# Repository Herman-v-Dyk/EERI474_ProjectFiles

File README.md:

All the files of my final year project is in this repository.

JH van Dyk
30254906

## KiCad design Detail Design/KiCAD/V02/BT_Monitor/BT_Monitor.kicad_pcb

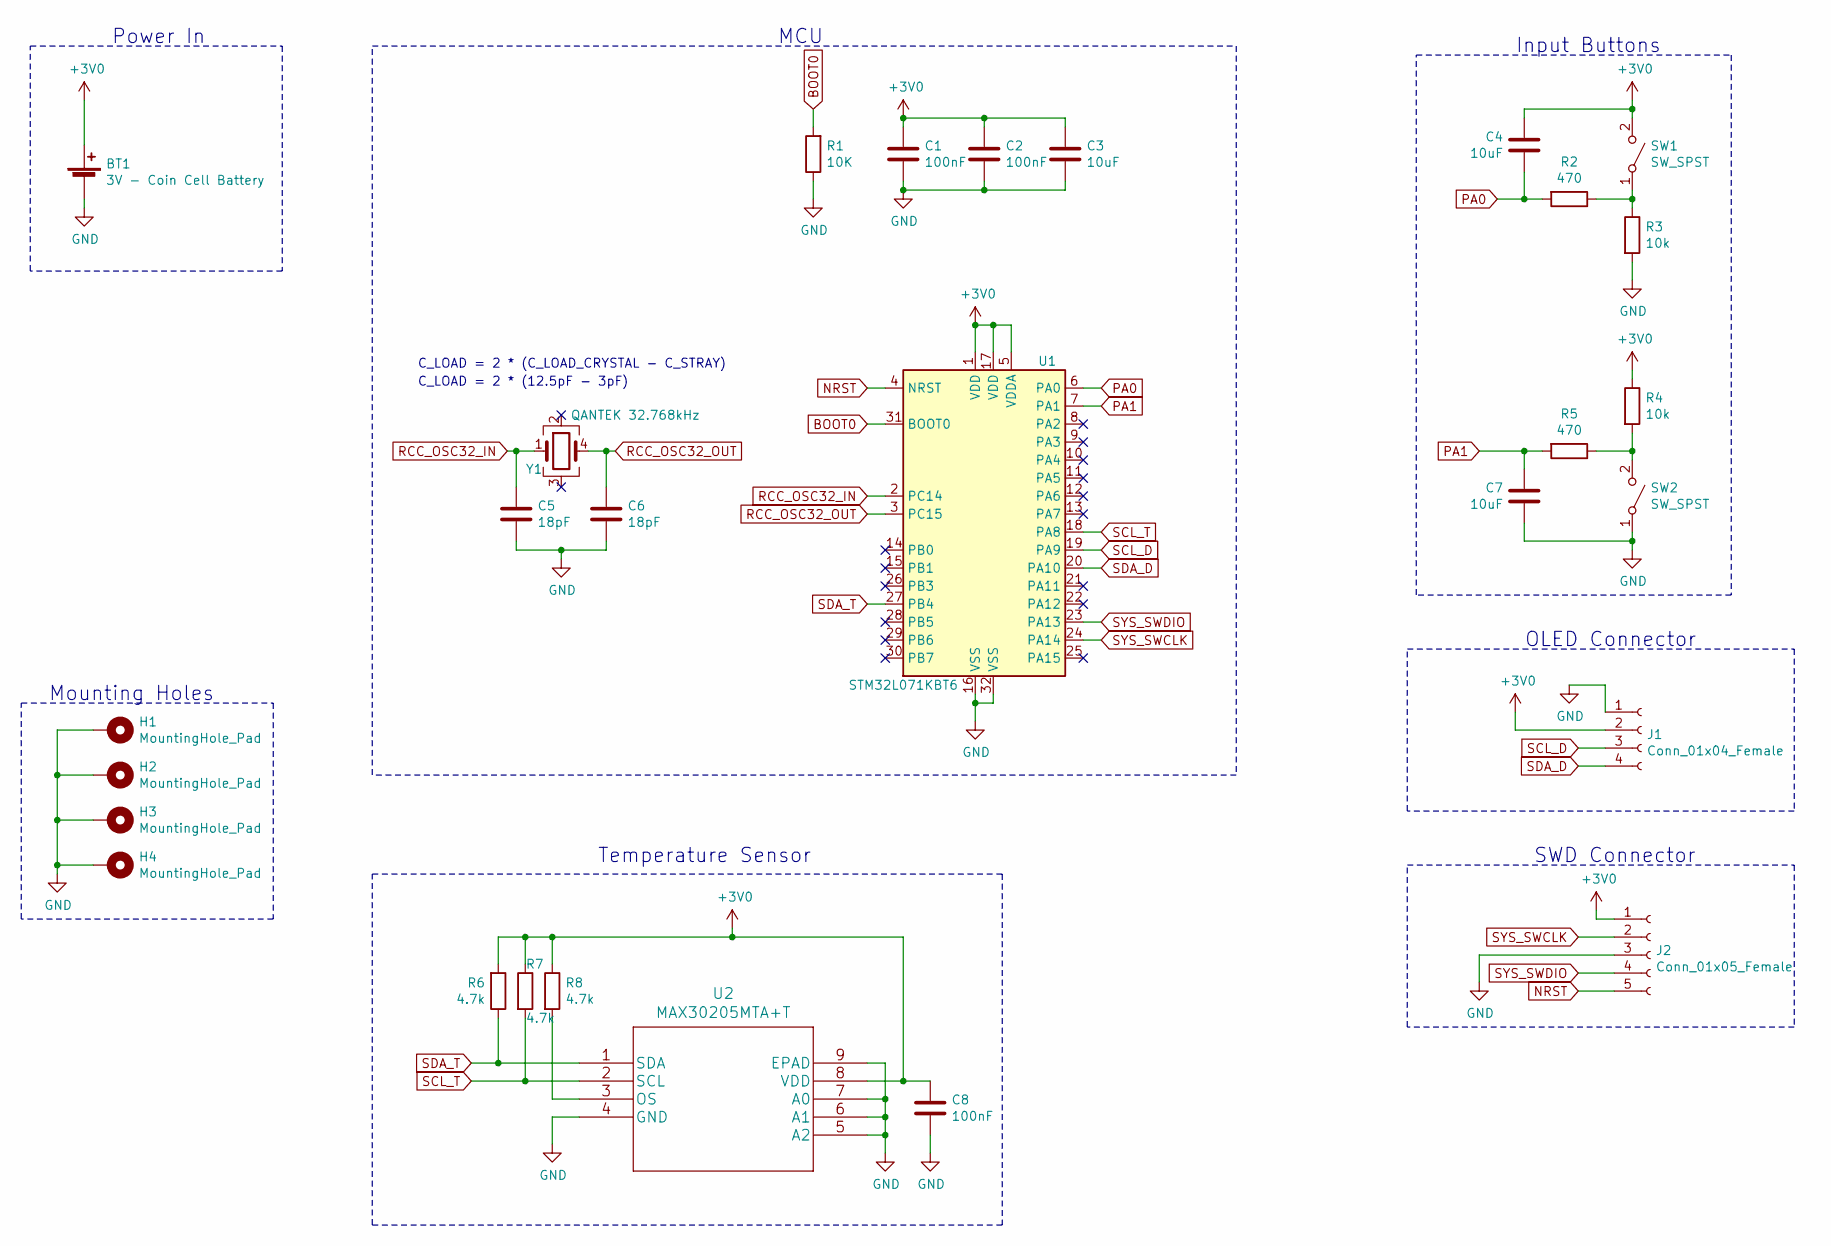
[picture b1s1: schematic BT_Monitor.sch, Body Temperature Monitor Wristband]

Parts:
BT1: 3V - Coin Cell Battery; BatteryHolder_Keystone_3002_1x2032
C1, C2, C8: 100nF; C_0805_2012Metric_Pad1.15x1.40mm_HandSolder
C3, C4, C7: 10uF; C_0805_2012Metric_Pad1.15x1.40mm_HandSolder
C5, C6: 18pF; C_0805_2012Metric_Pad1.15x1.40mm_HandSolder
H1, H2, H3, H4: MountingHole_Pad; MountingHole_2.2mm_M2_Pad
J1: Conn_01x04_Female; PinHeader_1x04_P2.54mm_Vertical
J2: Conn_01x05_Female; PinHeader_1x05_P2.54mm_Vertical
R1: 10K; R_0805_2012Metric_Pad1.15x1.40mm_HandSolder
R2, R5: 470; R_0603_1608Metric_Pad1.05x0.95mm_HandSolder
R3, R4: 10k; R_0805_2012Metric_Pad1.15x1.40mm_HandSolder
R6, R7, R8: 4.7k; R_0603_1608Metric_Pad1.05x0.95mm_HandSolder
SW1, SW2: SW_SPST; Tactile-Switch-SPST-SMD
U1: STM32L071KBT6; LQFP-32_7x7mm_P0.8mm
U2: MAX30205MTA+T; MAX30205
Y1: QANTEK 32.768kHz; Crystal_SMD_SeikoEpson_MC146-4Pin_6.7x1.5mm_HandSoldering

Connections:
+3V0: BT1.1 (+), C1.1, C2.1, C3.1, C4.2, C8.1, J1.2, J2.1, R4.1, R6.2, R7.1, R8.1, SW1.2 (B), U1.1 (VDD), U1.5 (VDDA), U1.17 (VDD), U2.8 (VDD)
BOOT0: R1.2, U1.31 (BOOT0)
GND: BT1.2 (-), C1.2, C2.2, C3.2, C5.2, C6.2, C7.1, C8.2, H1.1, H2.1, H3.1, H4.1, J1.1, J2.3, R1.1, R3.2, SW2.1 (A), U1.16 (VSS), U1.32 (VSS), U2.4 (GND), U2.5 (A2), U2.6 (A1), U2.7 (A0), U2.9 (EPAD)
NRST: J2.5, U1.4 (NRST)
unnamed: R2.1, R3.1, SW1.1 (A)
unnamed: R4.2, R5.1, SW2.2 (B)
unnamed: R8.2, U2.3 (OS)
PA0: C4.1, R2.2, U1.6 (PA0)
PA1: C7.2, R5.2, U1.7 (PA1)
RCC_OSC32_IN: C5.1, U1.2 (PC14), Y1.1
RCC_OSC32_OUT: C6.1, U1.3 (PC15), Y1.4
SCL_D: J1.3, U1.19 (PA9)
SCL_T: R7.2, U1.18 (PA8), U2.2 (SCL)
SDA_D: J1.4, U1.20 (PA10)
SDA_T: R6.1, U1.27 (PB4), U2.1 (SDA)
SYS_SWCLK: J2.2, U1.24 (PA14)
SYS_SWDIO: J2.4, U1.23 (PA13)

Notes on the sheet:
C_LOAD = 2 * (C_LOAD_CRYSTAL - C_STRAY)
C_LOAD = 2 * (12.5pF - 3pF)
MCU
Power In
Temperature Sensor
Input Buttons
OLED Connector
SWD Connector
Mounting Holes

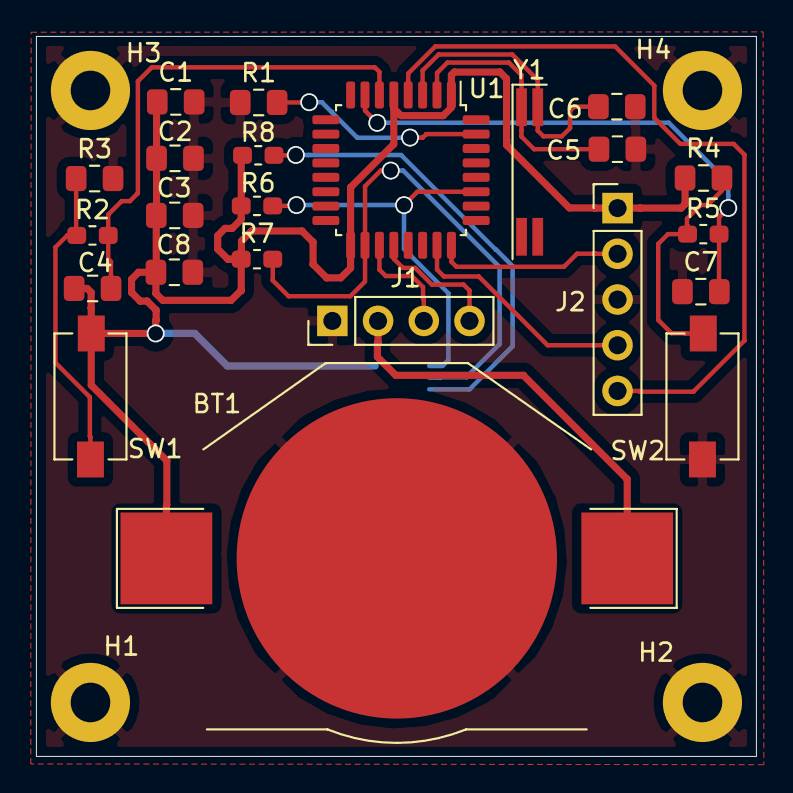
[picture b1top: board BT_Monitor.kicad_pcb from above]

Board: 2 copper layers, 40.0 x 40.0 mm, 28 parts (1 on the bottom side), 17 nets.

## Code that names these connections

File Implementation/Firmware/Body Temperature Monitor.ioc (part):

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Mcu.Name=STM32L071K(B-Z)Tx
Mcu.Package=LQFP32
Mcu.UserName=STM32L071KBTx
PA0.Mode=SYS_WakeUp0
PA0.Signal=SYS_WKUP1
PA10.Mode=I2C
PA10.Signal=I2C1_SDA
PA13.Mode=Serial_Wire
PA13.Signal=SYS_SWDIO
PA14.Mode=Serial_Wire
PA14.Signal=SYS_SWCLK
PA8.Mode=I2C
PA8.Signal=I2C3_SCL
PA9.Mode=I2C
PA9.Signal=I2C1_SCL
PB1.Signal=GPIO_Input
PB4.Mode=I2C
PB4.Signal=I2C3_SDA
PC14-OSC32_IN.Mode=LSE-External-Oscillator
PC14-OSC32_IN.Signal=RCC_OSC32_IN
PC15-OSC32_OUT.Mode=LSE-External-Oscillator
PC15-OSC32_OUT.Signal=RCC_OSC32_OUT
RCC.SYSCLKFreq_VALUE=16000000
RCC.SYSCLKSource=RCC_SYSCLKSOURCE_HSI
board=custom

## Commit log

2021-11-09 Create test

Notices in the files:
parts and their libraries:
Copyright 2021 Accelerated Designs. All rights reserved.
